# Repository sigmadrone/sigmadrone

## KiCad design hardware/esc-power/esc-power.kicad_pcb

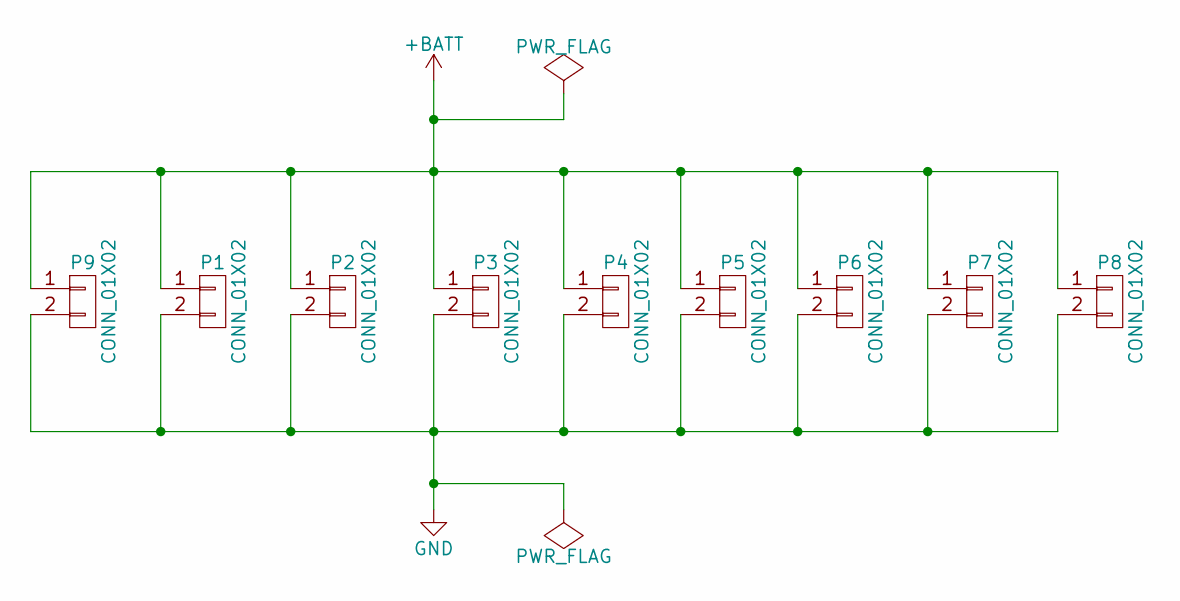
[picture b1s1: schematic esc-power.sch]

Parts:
P1, P2, P3, P4, P5, P6, P7, P8: CONN_01X02; TerminalBlock_Pheonix_PT-3.5mm_2pol
P9: CONN_01X02; WURTH_691219610002

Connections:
+BATT: P1.1, P2.1, P3.1, P4.1, P5.1, P6.1, P7.1, P8.1, P9.1
GND: P1.2, P2.2, P3.2, P4.2, P5.2, P6.2, P7.2, P8.2, P9.2

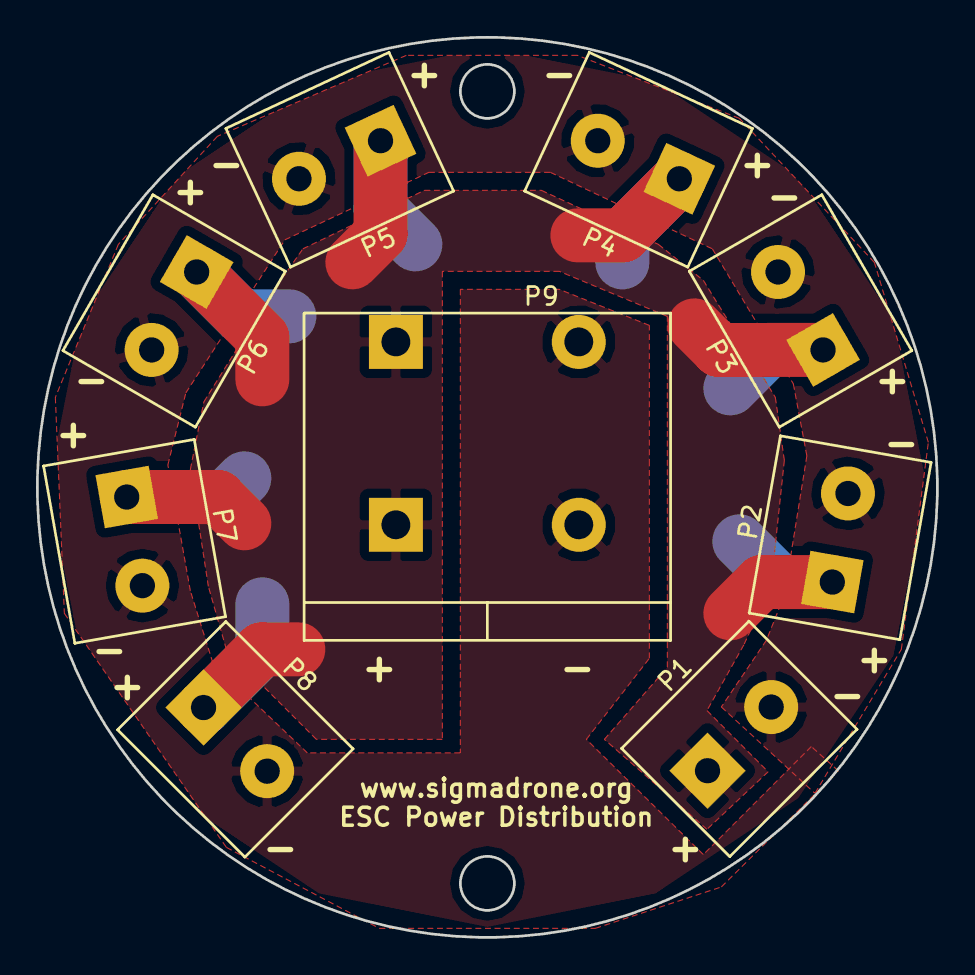
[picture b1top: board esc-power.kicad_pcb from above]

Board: 2 copper layers, 50.0 x 50.0 mm, 9 parts (0 on the bottom side), 2 nets.

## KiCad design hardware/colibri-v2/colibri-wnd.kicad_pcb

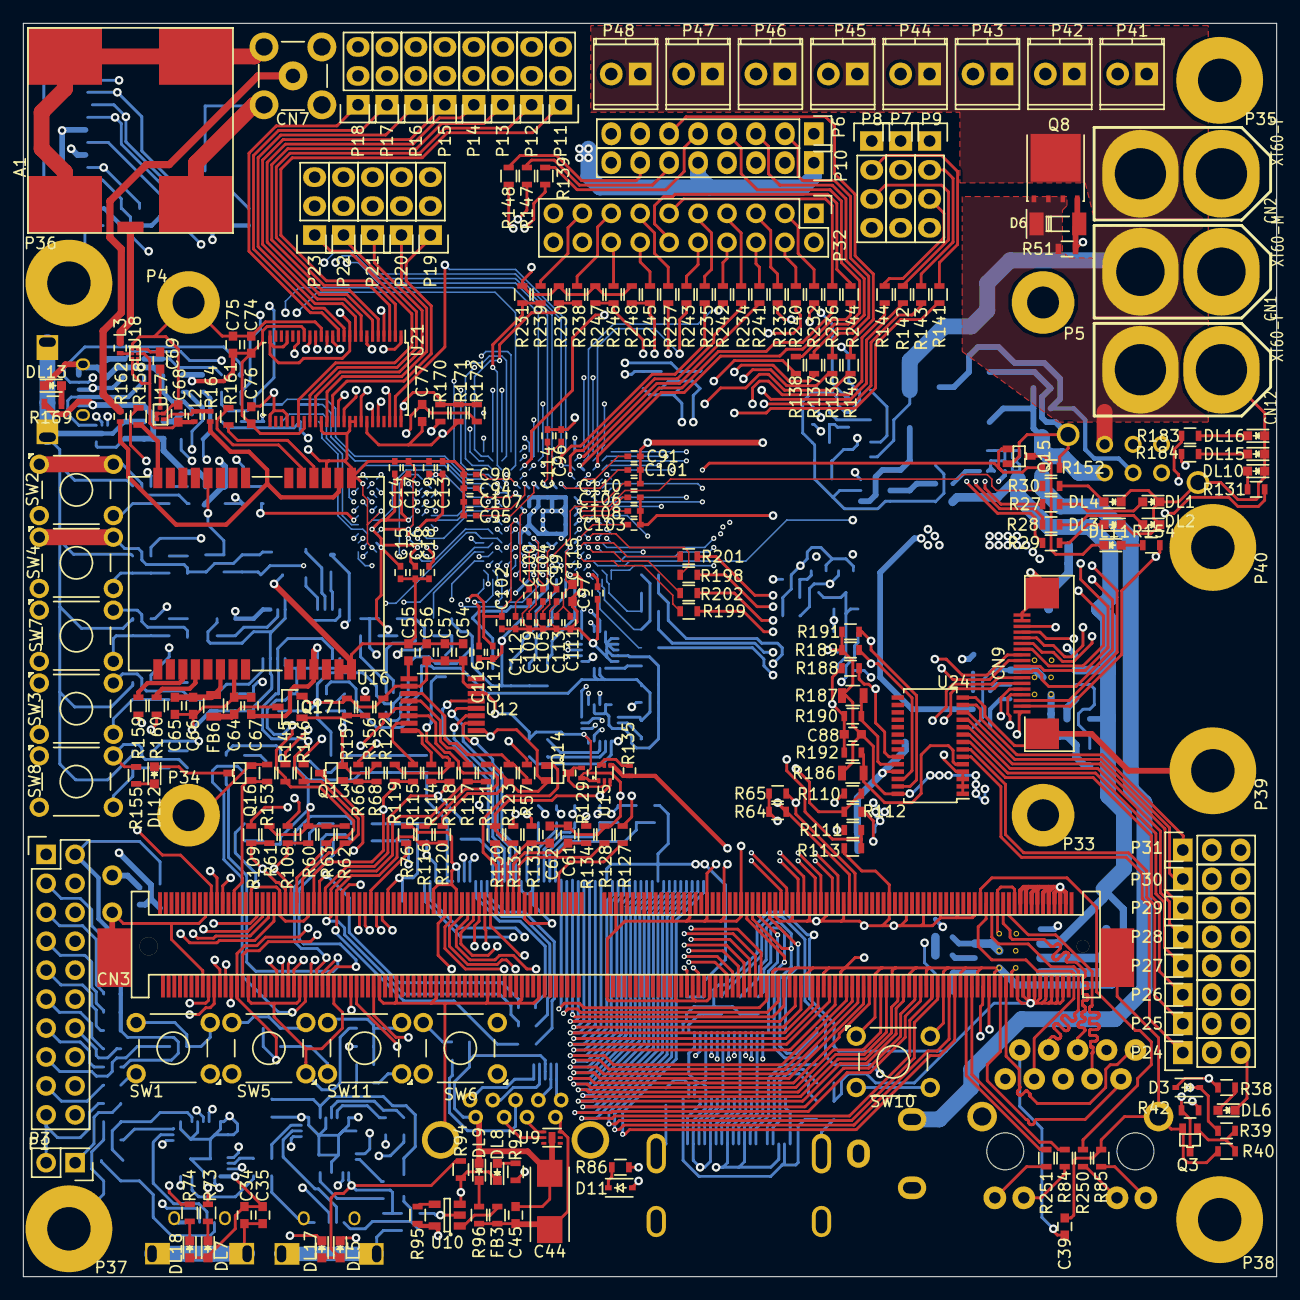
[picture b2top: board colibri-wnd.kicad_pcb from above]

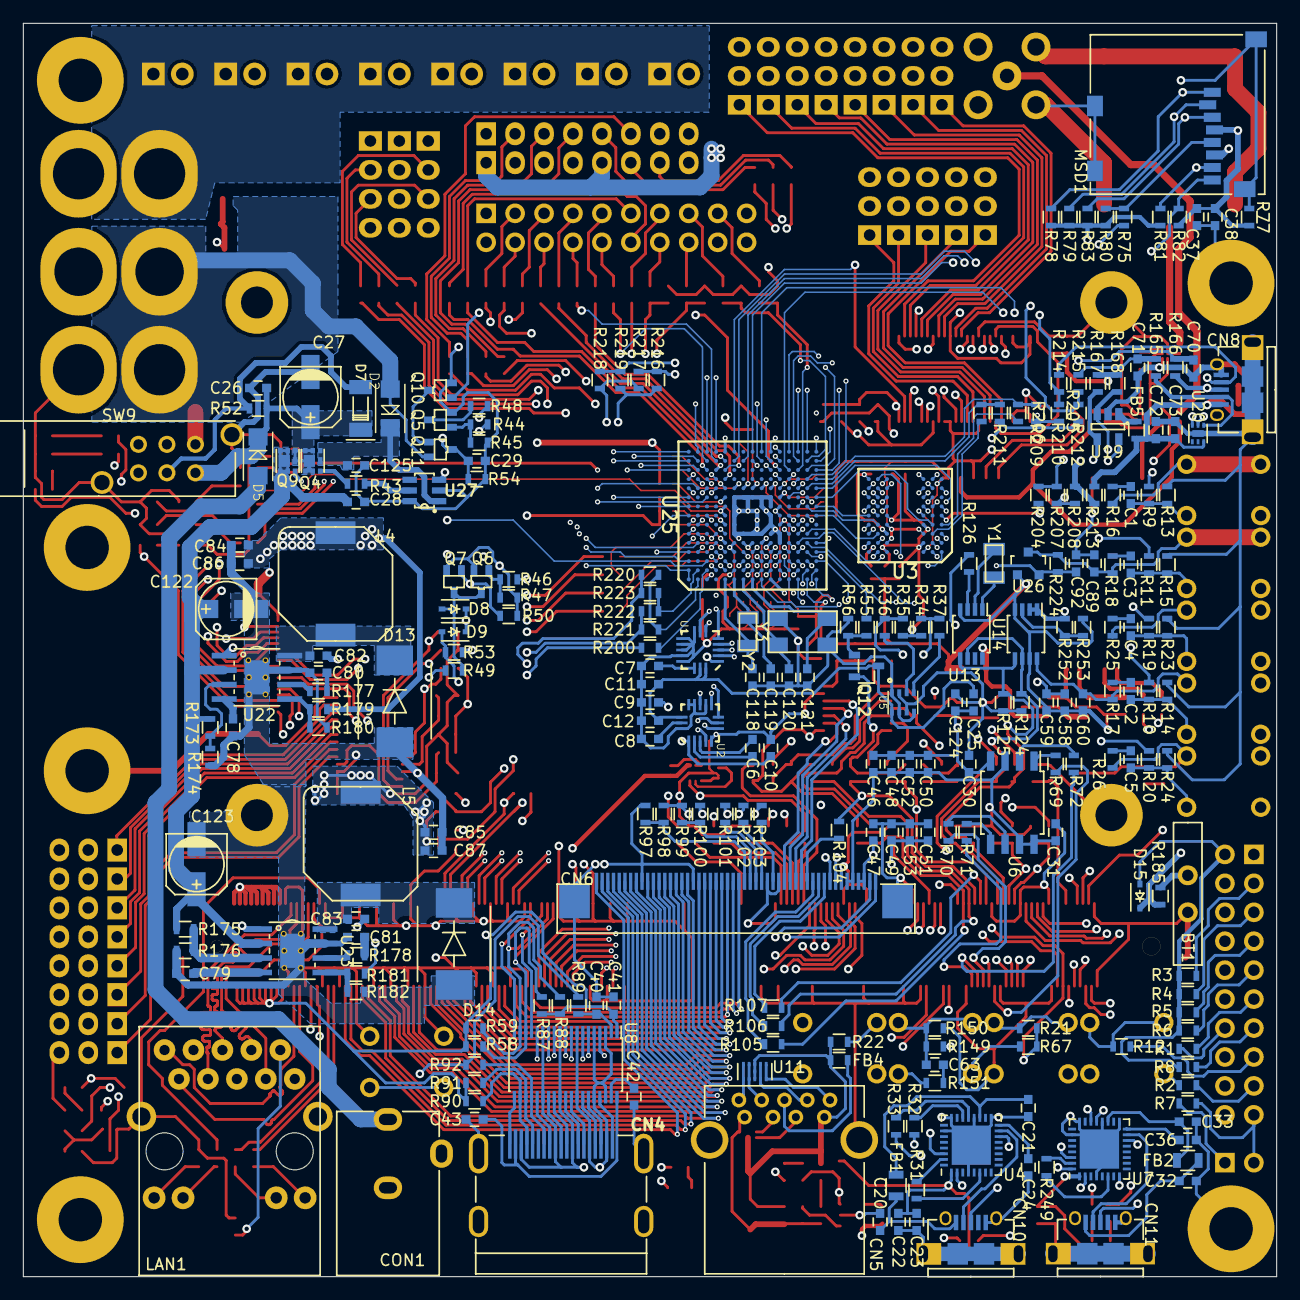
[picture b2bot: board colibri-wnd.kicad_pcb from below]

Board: 6 copper layers, 110.0 x 110.0 mm, 521 parts (247 on the bottom side), 486 nets.

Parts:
A1: ANT1818B00AT1575S
BT1: VL1220-1VC; VL_1220
C1, C2, C3, C4, C5, C25, C63, C92, C124: 100nF/50V; C_0603
C6: 220nF/50V/X7R; C_0603
C7: 10nF/50V/X7R; C_0603
C8: 4u7/6V3/X5R; C_0603
C9, C10, C21, C23, C24, C26, C28, C29, C31, C33, C35, C36, C37, C39, C40, C41, C42, C43, C45, C48, C49, C52, C53, C54, C55, C56, C59, C60, C66, C67, C68, C73, C74, C75, C76, C77, C78, C79, C82, C83, C89, C125: 100nF/50V/X7R; C_0603
C11, C12, C20, C22, C32, C34, C38, C58, C65, C72, C84, C85, C86, C87, C88, C115: 10uF/16V/X5R; C_0603
C13, C14, C15, C16, C17, C18, C19, C94, C95, C96, C97, C99, C100, C101, C102, C103, C104, C105, C106, C107, C108, C109, C110, C111, C112, C113, C114, C117: 100nF/16V; C_0402
C27, C122, C123: 22uF/35V; c_elec_5x5.7
C30: 2u2/10V/X5R; C_0603
C44: 220uF/10%/6V3; TantalC_SizeC_EIA-6032_Reflow
C46, C47: 47uF/25V/X7R; C_0603
C50, C51, C57, C64: 1uF/25V/X7R; C_0603
C61, C62, C70, C71: 47pF/100V/C0G; C_0603
C69: 100pF/50V/1%; C_0603
C80, C81: 470pF/50V/X7R; C_0603
C90, C91, C116: 2u2/10V; C_0402
C118, C119: 15pF/50V/NPO; C_0603
C120, C121: 10pF/50V/NPO; C_0603
CN1: XT60-M; xt60-M
CN2, CN12: XT60-F; xt60-F
CN3: AS0B821-S78B-7H
CN4: HDMI_A; MOLEX_500254_1927
CN5: 692_121_030_100; 692121030100
CN6: Wurth-68715014522-LCD; 68715014522
CN7: MOLEX_73366_0061
CN8, CN10, CN11: 629_105_150_921; WURTH_629105150921
CN9: Wurth-68711814522; 68711814522
CON1: PJ-102AH
D2, D5: VS-15MQ040NTRPBF; DO-214AC
D3, D8, D9, D11, D15: BAS316; SOD-323
D6, D7: BZV55-C18; SOD-80
D13, D14: B560C-13-F; DO-214AB-B560C-13-F
DL1, DL2, DL5, DL7, DL9, DL10, DL11, DL13, DL16: GREEN; LED_0603
DL3, DL4, DL6, DL8, DL12, DL15, DL17, DL18: RED; LED_0603
FB1, FB2: BEAD/0.6OHM/0.2A; R_0805
FB3, FB4, FB5: BEAD/0.045OHM/2A; R_0603
FB6: BEAD/330ohm/100MHz; R_0805
L2: 47nH/0A2/5%; R_0402
L3: 5.6nH/800mA/±0.5nH/0402; R_0402
L4, L5: 3u3/4A6; 7447713033
LAN1: 7499111446; WURTH_7499111446
MSD1: WURTH_693071010811
P1, P32: CONN_02X10; Pin_Header_Straight_2x10
P3: CONN_02X01; Pin_Header_Straight_2x01
P4, P5, P33, P34: ECM00870-L
P6, P10: CONN_01X08; Pin_Header_Straight_1x08
P7, P8, P9: CONN_01X04; Pin_Header_Straight_1x04
P11, P12, P13, P14, P15, P16, P17, P18, P19, P20, P21, P22, P23, P24, P25, P26, P27, P28, P29, P30, P31: CONN_01X03; Pin_Header_Straight_1x03
P35, P36, P37, P38, P39, P40: STANDOFF; STANDOFF-6-32
P41, P42, P43, P44, P45, P46, P47, P48: MPT-2.54; TerminalBlock_Pheonix_MPT-2.54mm_2pol
Q3, Q5, Q6, Q7, Q13, Q15, Q16: BSS138PW; SOT-323
Q4, Q9: FDMA530PZ
Q8: AP6681GMT-HF-3TR; AP6681GMT-HF-3
Q10: PDTC123JU; SOT-323
Q11, Q14: PDTA123JU; SOT-323
Q12, Q17: IRLML6402TRPBF; SOT23_IRLML6402
R1, R2, R3, R4, R5, R6, R8, R22, R39, R40, R42, R45, R47, R49, R51, R53, R67, R68, R76, R77, R78, R79, R80, R81, R82, R83, R89, R94, R95, R112, R113, R118, R119, R120, R121, R122, R123, R127, R152, R153, R167, R168, R188, R190, R192, R224: 10K/5%; R_0603
R7, R57, R85, R126, R128, R198, R199, R200, R201, R202, R204, R205, R206, R208, R210, R212, R217, R219, R221, R223, R249, R251, R252: 0R/5%; R_0603
R9, R10, R11, R12, R16, R17, R18, R19, R20, R21, R25, R26, R43, R44, R46, R48, R66, R149, R151: 100R/5%; R_0603
R13, R14, R15, R23, R24, R50, R52, R54, R56, R150: 100K/5%; R_0603
R27, R28, R29, R30, R86: 1K/5%; R_0603
R31, R98: N/A; R_0603
R32, R33, R73, R74: 270R/5%; R_0603
R34, R35, R38, R58, R59, R60, R61, R62, R63, R64, R65, R87, R88, R189, R191, R230, R231, R247, R248: 2k2/5%; R_0603
R36, R37, R55, R69, R70, R71, R72, R75, R97, R99, R100, R101, R102, R103, R104, R105, R106, R107, R108, R109, R110, R111, R114, R115, R116, R117, R130, R132, R133, R134, R136, R137, R138, R139, R140, R141, R142, R143, R144, R145, R146, R147, R148, R156, R158, R159, R160, R165, R166, R232, R233, R234, R235, R236, R237, R238, R239, R240, R241, R242, R243, R244, R245, R246: 22R/5%; R_0603
R84, R250: 330R/5%; R_0603
R90, R91: 1k8/5%; R_0603
R92: 27K/5%; R_0603
R93: 620R/5%; R_0603
R96, R169: 1k2/5%; R_0603
R124, R125: 2k2/5% [NA]; R_0603
R129: 100K/1%; R_0402
R131: 1k1/5%; R_0603
R135: 47K/1%; R_0402
R154: 360R; R_0603
R155: 750R; R_0603
R157: 100k/5%; R_0603
R161: 10R/5%; R_0603
R162, R164: 0R/5%; R_0402
R170: 0R[NA]; R_0603
R171: 10K/5%[NA]; R_0603
R172: 0R; R_0603
R173, R174, R175, R176, R177, R178: 150K/5%; R_0603
R179, R181: 10K2/1%; R_0603
R180: 1K96/1%; R_0603
R182: 3K24/1%; R_0603
R183: 1k5/5%; R_0603
R184: 750R/5%; R_0603
R185: 470R/5%; R_0603
R186, R187: 0R/1%; R_0805
R207, R209, R211, R213, R214, R215, R216, R218, R220, R222, R253: 0R/5%[NA]; R_0603
SW1, SW2, SW3, SW4, SW5, SW6, SW7, SW8, SW10, SW11: OMRON B3F-1070; SW_TH_Tactile_Omron_B3F-10xx_6x6
SW9: ALPS-SPPJ320600; SPPJ320600
U1: L3GD20HTR; LGA16-3MM_LONG_PADS
U2: LSM303DTR; LGA16-3MM_LONG_PADS
U3: IS42S16400J-7BLI; tfbga-54-35
U4, U7: FT232RQ; QFN-32-1EP_5x5mm_Pitch0.5mm
U5: BMP280; BMP280_LGA-8
U6: M25P32-VMW6TG; SOIJ-8_5.3x5.3mm_Pitch1.27mm
U8: TPD12S521DBTR; TSSOP-38_4.4x9.7mm_Pitch0.5mm
U9, U20: VBUS053CZ-HAF-G-08; VBUS053CZ-HAF
U10: TPS2065CDBVT; SOT-23-5
U11: VBUS054CD-FHI-GS08; VBUS054CD-FHI
U12: TSC2046IPWR; TSSOP-16_4.4x5mm_Pitch0.65mm
U13: PCF8563TS; TSSOP-8_3x3mm_Pitch0.65mm
U14: BR24L02FVM-WTR; TSSOP-8_3x3mm_Pitch0.65mm
U15: NTZD3155C; SOT-563_NTZD3155C
U16: LEA-6S; LEA-6
U17: SF1186K-3
U18: BGA825L6S; TSLP-6-3
U19: TPS2061CDBVT; SOT-23-5
U21: SN74LVC162244A; TSSOP-48_6.1x12.5mm_Pitch0.5mm
U22, U23: TPS54332DDA; TPS54332DDAR
U24: PCA9685PW; TSSOP-28_4.4x9.7mm_Pitch0.65mm
U25: STM32F429NI; tfbga-216-35
U26: TLV803SDBZT; SOT-23
U27: LTC4412; SOT23-6_LTC4412
Y1, Y2: 32.768KHZ; ABS07
Y3: ABMM2-MHz; ABMM2

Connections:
+3V3: C9.1, C10.1, C13.1, C14.1, C15.1, C16.1, C17.1, C18.1, C19.1, C22.2, C23.2, C30.1, C31.2, C34.2, C35.2, C37.1, C38.1, C46.1, C48.1, C50.1, C52.1, C54.1, C56.1, C57.1, C60.2, C74.1, C75.1, C76.1, C77.1, C85.1, C87.1, C88.2, C89.2, C94.2, C95.2, C96.2, C99.2, C100.2, C101.2, C102.2, C103.2, C104.2, C105.2, C106.2, C107.2, C108.2, C109.2, C110.2, C111.2, C112.2, C113.2, C114.2, C115.1, C116.2, C117.1, C124.1, CN6.45, CN6.46, CN9.1, D11.2, D15.2, DL5.2, DL7.2, DL17.2, DL18.2, L5.2, MSD1.4, P1.1, P1.2, P6.1, P7.1, P9.1, P10.1, P10.5, P32.1, P32.2, Q12.2, Q14.2, Q17.2, R3.1, R4.1, R5.1, R6.1, R8.1, R16.1, R17.1, R18.1, R25.1, R26.1, R34.1, R35.1, R42.1, R53.1, R60.1, R61.1, R62.1, R63.1, R64.1, R65.1, R67.1, R77.1, R78.1, R79.1, R80.1, R81.1, R82.1, R83.1, R89.1, R92.1, R93.1, R94.1, R112.2, R118.1, R119.1, R120.1, R121.1, R122.1, R123.1, R124.1, R125.1, R127.1, R151.1, R154.1, R155.1, R157.1, R167.1, R168.1, R171.1, R181.1, R184.1, R186.2, R187.2, R189.1, R191.1, R224.1, R230.1, R231.1, R247.1, R248.1, R252.1, SW2.1, SW2.2, SW3.1, SW3.2, SW4.1, SW4.2, SW6.1, SW6.2, SW7.1, SW7.2, SW8.1, SW8.2, SW11.1, SW11.2, U1.1, U2.1, U3.A7, U3.A9, U3.B3, U3.C7, U3.D3, U3.E7, U3.J9, U4.1, U5.2, U5.6, U6.3, U6.7, U6.8, U7.1, U12.1, U12.7, U12.10, U14.1, U14.2, U14.8, U21.7, U21.18, U21.31, U21.42, U24.28, U25.E5, U25.E7, U25.E8, U25.E9, U25.E10, U25.F4, U25.F5, U25.F11, U25.G5, U25.G11, U25.H5, U25.H11, U25.J5, U25.J11, U25.K5, U25.K11, U25.L7, U25.L8, U25.L9, U25.L10, U25.P1, U25.R1, U26.3
+5V: C41.2, C47.1, C49.1, C51.1, C53.1, C84.1, C86.1, CN3.1E2, CN3.1E3, CN3.1E4, CN3.1E5, CN3.1E6, CN3.1E7, CN3.1E8, CN3.1E9, CN3.1E10, CN3.2E2, CN3.2E3, CN3.2E4, CN3.2E5, CN3.2E6, CN3.2E7, CN3.2E8, CN3.2E9, CN3.2E10, CN6.47, CN6.48, L4.2, P7.4, P8.1, P11.2, P12.2, P13.2, P14.2, P15.2, P16.2, P17.2, P18.2, P19.2, P20.2, P21.2, P22.2, P23.2, P24.2, P25.2, P26.2, P27.2, P28.2, P29.2, P30.2, P31.2, R58.1, R59.1, R87.1, R88.1, R90.1, R91.1, R95.1, R135.2, R179.1, R183.2, U8.1, U10.5, U15.4, U19.5
+BATT: CN1.P, CN12.P, D2.2, D6.1, Q8.1, Q8.2, Q8.3, Q11.2, R51.1, SW9.4
/Cortex FTDI Interface/C_FTDI_RXD: U4.2, U25.B6
/Cortex FTDI Interface/C_FTDI_TXD: U4.30, U25.B5
/External Sensors/C_I2C2_SCL: R246.1, R247.2, U25.H4
/External Sensors/C_I2C2_SDA: R245.1, R248.2, U25.J3
/External Sensors/C_I2C3_SCL: R231.2, R239.1, U25.N13
/External Sensors/C_I2C3_SDA: R230.2, R238.1, U25.P14
/External Sensors/C_SPI2_CLK: R242.1, U25.D14
/External Sensors/C_SPI2_MISO: R243.1, U25.C14
/External Sensors/C_SPI2_MOSI: R244.1, U25.C13
/External Sensors/C_SPI2_NSS1: R241.1, U25.E14
/External Sensors/C_SPI2_NSS2: R240.1, U25.C3
/External Sensors/EXT_GPIO_1: R232.1, U25.P13
/External Sensors/EXT_GPIO_2: R233.1, U25.M15
/External Sensors/EXT_GPIO_3: R234.1, U25.E12
/External Sensors/EXT_GPIO_4: R235.1, U25.E13
/External Sensors/EXT_GPIO_5: R236.1, U25.D13
/External Sensors/EXT_GPIO_6: R237.1, U25.K2
/GPS/GPS_RXD(3V3): R160.2, U25.B14
/GPS/GPS_TIME_PULSE: R158.2, U25.A8
/JTAG/SWD/JTAG_POWER: P1.19, P3.2, R7.2
/JTAG/SWD/JTAG_POWER_ON: P3.1, R7.1, R46.2
/JTAG/SWD/RESET#: C92.1, P1.15, R12.2, R224.2, U25.J1, U26.2
/JTAG/SWD/TCK/SWCLK: P1.9, R6.2, U25.A14
/JTAG/SWD/TDI: P1.5, R4.2, U25.A13
/JTAG/SWD/TDO/SWO: P1.13, R8.2, U25.A10
/JTAG/SWD/TMS/SWDIO: P1.7, R5.2, U25.A15
/JTAG/SWD/TRST: P1.3, R3.2, U25.A9
/Leds/Buttons/BOOT0: R22.2, SW6.3, SW6.4, U25.E6
/Leds/Buttons/BUTTON_0: R9.2, U25.M5
/Leds/Buttons/BUTTON_1: R10.2, U25.M13
/Leds/Buttons/BUTTON_2: R11.2, U25.M12
/Leds/Buttons/BUTTON_3: R19.2, U25.J15
/Leds/Buttons/BUTTON_4: R20.2, U25.J14
/Leds/Buttons/LED1: R27.2, U25.E3
/Leds/Buttons/LED2: R28.2, U25.G3
/Leds/Buttons/LED3: R29.2, U25.H3
/Leds/Buttons/LED4: R30.2, U25.G4
/Leds/Buttons/MODULE_RESET#: CN3.254, R21.2, R67.2, U25.N4
/MEMS/MEMS_ACC_INT1: U2.11, U25.D12
/MEMS/MEMS_ACC_INT2: U2.9, U25.A12
/MEMS/MEMS_GYR_INT1: U1.7, U25.N2
/MEMS/MEMS_GYR_INT2: U1.6, U25.R2
/MEMS/V_SENS1: C11.1, C12.1, C25.1, Q12.3, U1.15, U1.16, U2.14, U5.8
/Power Control/ADAPTER_AV#: Q3.3, R42.2, U25.L4
/Power Control/BAT_MSRMNT: C29.1, Q11.3, R54.1, U25.M4
/Power Control/MSRMNT_ON: Q10.1, U25.N14
/Power Control/PWR_BTN_READ: D9.2, R53.2, U25.P15
/Power Control/PWR_ON: Q7.1, R50.1, U25.N15
/Power Control/VH_CTRL: R44.2, U25.R5
/Power Control/Vsys: C28.1, C122.1, C123.1, Q9.1, Q9.2, Q9.5, Q9.6, Q9.7, R173.1, R175.1, U22.2, U23.2
/STM32F4 SDRAM/FMC_A0: U3.H7, U25.D2
/STM32F4 SDRAM/FMC_A1: U3.H8, U25.E2
/STM32F4 SDRAM/FMC_A2: U3.J8, U25.G2
/STM32F4 SDRAM/FMC_A3: U3.J7, U25.H2
/STM32F4 SDRAM/FMC_A4: U3.J3, U25.J2
/STM32F4 SDRAM/FMC_A5: U3.J2, U25.K3
/STM32F4 SDRAM/FMC_A6: U3.H3, U25.M6
/STM32F4 SDRAM/FMC_A7: U3.H2, U25.N6
/STM32F4 SDRAM/FMC_A8: U3.H1, U25.P6
/STM32F4 SDRAM/FMC_A9: U3.G3, U25.M8
/STM32F4 SDRAM/FMC_A10: U3.H9, U25.N7
/STM32F4 SDRAM/FMC_A11: U3.G2, U25.M7
/STM32F4 SDRAM/FMC_B0: U3.G7, U25.N12
/STM32F4 SDRAM/FMC_B1: U3.G8, U25.N11
/STM32F4 SDRAM/FMC_D0: U3.A8, U25.L12
/STM32F4 SDRAM/FMC_D1: U3.B9, U25.K13
/STM32F4 SDRAM/FMC_D2: U3.B8, U25.B12
/STM32F4 SDRAM/FMC_D3: U3.C9, U25.C12
/STM32F4 SDRAM/FMC_D4: U3.C8, U25.R8
/STM32F4 SDRAM/FMC_D5: U3.D9, U25.N9
/STM32F4 SDRAM/FMC_D6: U3.D8, U25.P9
/STM32F4 SDRAM/FMC_D7: U3.E9, U25.R9
/STM32F4 SDRAM/FMC_D8: R204.2, U3.E1
/STM32F4 SDRAM/FMC_D9: U3.D2, U25.R10
/STM32F4 SDRAM/FMC_D10: R205.2, U3.D1
/STM32F4 SDRAM/FMC_D11: R206.2, U3.C2
/STM32F4 SDRAM/FMC_D12: U3.C1, U25.R11
/STM32F4 SDRAM/FMC_D13: U3.B2, U25.L15
/STM32F4 SDRAM/FMC_D14: U3.B1, U25.L14
/STM32F4 SDRAM/FMC_D15: U3.A2, U25.K15
/STM32F4 SDRAM/FMC_NBL0: U3.E8, U25.A6
/STM32F4 SDRAM/FMC_NBL1: U3.F1, U25.A5
/STM32F4 SDRAM/FMC_SDCKE0: U3.F3, U25.K4
/STM32F4 SDRAM/FMC_SDCLK: U3.F2, U25.H14
/STM32F4 SDRAM/FMC_SDNCAS: U3.F7, U25.B7
/STM32F4 SDRAM/FMC_SDNE0: U3.G9, U25.J4
/STM32F4 SDRAM/FMC_SDNRAS: U3.F8, U25.P8
/STM32F4 SDRAM/FMC_SDNWE: U3.F9, U25.M2
/Sensors Power Control/V_SENS_CTRL: R55.2, U25.R4
/Servo Motors PWM output/SRV_PWM_0: U21.47, U25.F15
/Servo Motors PWM output/SRV_PWM_1: R207.2, R208.2, U21.46
/Servo Motors PWM output/SRV_PWM_2: R209.2, R210.2, U21.44
/Servo Motors PWM output/SRV_PWM_3: R211.2, R212.2, U21.43
/Servo Motors PWM output/SRV_PWM_4: U21.41, U25.H15
/Servo Motors PWM output/SRV_PWM_6: U21.38, U25.G14
/Servo Motors PWM output/SRV_PWM_7: U21.37, U25.F14
/USB_OTG_FS/OTG_FS_DM: C71.1, R165.2, R215.2
/USB_OTG_FS/OTG_FS_DP: C70.1, R166.2, U25.B15
/USB_OTG_FS/OTG_FS_ID: CN8.4, R214.2, U20.3
/USB_OTG_FS/OTG_FS_VBUS: C72.1, C73.1, CN8.1, FB5.2, R169.2, R213.2, U20.6
/Wandboard Connector/CSPI1_CS1: CN3.230, R69.1
/Wandboard Connector/DISP0_DAT0: CN3.2, CN6.1
/Wandboard Connector/DISP0_DAT1: CN3.4, CN6.2
/Wandboard Connector/DISP0_DAT2: CN3.8, CN6.3
/Wandboard Connector/DISP0_DAT3: CN3.10, CN6.4
/Wandboard Connector/DISP0_DAT4: CN3.14, CN6.5
/Wandboard Connector/DISP0_DAT5: CN3.16, CN6.6
/Wandboard Connector/DISP0_DAT6: CN3.20, CN6.7
/Wandboard Connector/DISP0_DAT7: CN3.22, CN6.8
/Wandboard Connector/DISP0_DAT8: CN3.26, CN6.10
/Wandboard Connector/DISP0_DAT9: CN3.28, CN6.11
/Wandboard Connector/DISP0_DAT10: CN3.32, CN6.12
/Wandboard Connector/DISP0_DAT11: CN3.34, CN6.13
/Wandboard Connector/DISP0_DAT12: CN3.36, CN6.14
/Wandboard Connector/DISP0_DAT13: CN3.38, CN6.15
/Wandboard Connector/DISP0_DAT14: CN3.40, CN6.16
/Wandboard Connector/DISP0_DAT15: CN3.44, CN6.17
/Wandboard Connector/DISP0_DAT16: CN3.46, CN6.19
/Wandboard Connector/DISP0_DAT17: CN3.50, CN6.20
/Wandboard Connector/DISP0_DAT18: CN3.52, CN6.21
/Wandboard Connector/DISP0_DAT19: CN3.56, CN6.22
/Wandboard Connector/DISP0_DAT20: CN3.58, CN6.23
/Wandboard Connector/DISP0_DAT21: CN3.62, CN6.24
/Wandboard Connector/DISP0_DAT22: CN3.64, CN6.25
/Wandboard Connector/DISP0_DAT23: CN3.68, CN6.26
/Wandboard Connector/MODULE_ON/OFF: R66.2, U25.R3
/Wandboard Connector/PWR_BTN(ON/OFF): CN3.252, Q13.3
/Wandboard Connector/RTC_INT: CN3.96, R126.1, U25.C8
/Wandboard Connector/R_NANDF_CS2: CN3.92, R57.1
/Wandboard Connector/WB_GPIO1: CN3.256, R198.2
/Wandboard Connector/WB_GPIO2: CN3.258, R199.2
/Wandboard Connector/WB_GPIO3: CN3.260, R200.2
/Wandboard Connector/WB_GPIO4: CN3.262, R201.2
/Wandboard Connector/WB_GPIO5: CN3.264, R202.2
/Wandboard Connector/WB_SPI_CLK: CN3.226, R70.1, U25.A3
/Wandboard Connector/WB_SPI_CS: CN3.228, U25.A1, U25.A2
/Wandboard Connector/WB_SPI_MISO: CN3.224, R72.1, R221.2, R222.2
/Wandboard Connector/WB_SPI_MOSI: CN3.222, R71.1, R220.2, R223.2
/Wandboard Connector/Wandboard EEPROM/EEPROM_SCL: CN3.231, R62.2, R124.2, R146.1, U13.6, U14.6
/Wandboard Connector/Wandboard EEPROM/EEPROM_SDA: CN3.233, R63.2, R125.2, R145.1, U13.5, U14.5
/Wandboard Connector/Wandboard Ethernet/LED1_ACT: CN3.3E7, R250.2
/Wandboard Connector/Wandboard Ethernet/LED1_nLINK100: CN3.4E8, R84.2
/Wandboard Connector/Wandboard Ethernet/LED1_nLINK1000: CN3.4E9, R251.2
/Wandboard Connector/Wandboard Ethernet/TRD0_N: CN3.4E3, LAN1.2
/Wandboard Connector/Wandboard Ethernet/TRD0_P: CN3.4E2, LAN1.1
/Wandboard Connector/Wandboard Ethernet/TRD1_N: CN3.4E6, LAN1.6
/Wandboard Connector/Wandboard Ethernet/TRD1_P: CN3.4E5, LAN1.3
/Wandboard Connector/Wandboard Ethernet/TRD2_N: CN3.3E3, LAN1.5
/Wandboard Connector/Wandboard Ethernet/TRD2_P: CN3.3E2, LAN1.4
/Wandboard Connector/Wandboard Ethernet/TRD3_N: CN3.3E6, LAN1.8
/Wandboard Connector/Wandboard Ethernet/TRD3_P: CN3.3E5, LAN1.7
/Wandboard Connector/Wandboard FTDI Interface/WB_FTDI_CTS: CN3.241, U7.8
/Wandboard Connector/Wandboard FTDI Interface/WB_FTDI_DSR: R249.1, U7.6
/Wandboard Connector/Wandboard FTDI Interface/WB_FTDI_DTR: R249.2, U7.31
/Wandboard Connector/Wandboard FTDI Interface/WB_FTDI_RTS: CN3.247, U7.32
/Wandboard Connector/Wandboard FTDI Interface/WB_FTDI_RXD: CN3.243, U7.2
/Wandboard Connector/Wandboard FTDI Interface/WB_FTDI_TXD: CN3.245, U7.30
/Wandboard Connector/Wandboard HDMI/DDC_SCL(5V): CN3.75, R58.2, R87.2, R141.1, U8.17
/Wandboard Connector/Wandboard HDMI/HDMI1_HPD: CN3.67, U8.19
/Wandboard Connector/Wandboard HDMI/HDMI_CEC_IN: CN3.71, R86.2, U8.16
/Wandboard Connector/Wandboard HDMI/HDMI_CLK+: CN3.43, U8.13
/Wandboard Connector/Wandboard HDMI/HDMI_CLK-: CN3.45, U8.15
/Wandboard Connector/Wandboard HDMI/HDMI_D0+: CN3.49, U8.10
/Wandboard Connector/Wandboard HDMI/HDMI_D0-: CN3.51, U8.12
/Wandboard Connector/Wandboard HDMI/HDMI_D1+: CN3.55, U8.7
/Wandboard Connector/Wandboard HDMI/HDMI_D1-: CN3.57, U8.9
/Wandboard Connector/Wandboard HDMI/HDMI_D2+: CN3.61, U8.4
/Wandboard Connector/Wandboard HDMI/HDMI_D2-: CN3.63, U8.6
/Wandboard Connector/Wandboard LCD/DISP0_CLK: CN3.70, R103.2
/Wandboard Connector/Wandboard LCD/DISP0_CNTRST: CN3.76, R98.2, R99.2
/Wandboard Connector/Wandboard LCD/DISP0_DRDY: CN3.78, R100.2
/Wandboard Connector/Wandboard LCD/DISP0_HSYNC: CN3.72, R101.2
/Wandboard Connector/Wandboard LCD/DISP0_PWREN: CN3.82, R111.2
/Wandboard Connector/Wandboard LCD/DISP0_RESET: CN3.80, R110.2
/Wandboard Connector/Wandboard LCD/DISP0_VSYNC: CN3.74, R102.2
/Wandboard Connector/Wandboard LCD/TOUCH_X1: CN6.34, U12.2
/Wandboard Connector/Wandboard LCD/TOUCH_X2: CN6.35, U12.4
/Wandboard Connector/Wandboard LCD/TOUCH_Y1: CN6.36, U12.3
/Wandboard Connector/Wandboard LCD/TOUCH_Y2: CN6.37, U12.5
/Wandboard Connector/Wandboard LCD/TP_BUSY: CN3.263, R122.2, U12.13
/Wandboard Connector/Wandboard LCD/TP_PENIRQ: R57.2, R123.2, U12.11
/Wandboard Connector/Wandboard OTG to Cortex USB FS2/USB_OGT_DM: C62.1, CN3.159, R133.2
/Wandboard Connector/Wandboard OTG to Cortex USB FS2/USB_OTG_DP: C61.1, CN3.157, R134.2
/Wandboard Connector/Wandboard OTG to Cortex USB FS2/USB_OTG_ID: CN3.155, R128.2
/Wandboard Connector/Wandboard OTG to Cortex USB FS2/USB_OTG_OC: CN3.141, R127.2
/Wandboard Connector/Wandboard OTG to Cortex USB FS2/USB_OTG_PWR_EN#: CN3.163, Q14.1
/Wandboard Connector/Wandboard OTG to Cortex USB FS2/USG_OTG_VBUS: CN3.161, R130.2
/Wandboard Connector/Wandboard SD Card/SD1_CD: CN3.203, MSD1.9, R77.2
/Wandboard Connector/Wandboard SD Card/SD1_CLK: CN3.206, R75.2
/Wandboard Connector/Wandboard SD Card/SD1_CMD: CN3.205, MSD1.3, R83.2
/Wandboard Connector/Wandboard SD Card/SD1_DATA0: CN3.212, MSD1.7, R81.2
/Wandboard Connector/Wandboard SD Card/SD1_DATA1: CN3.209, MSD1.8, R82.2
/Wandboard Connector/Wandboard SD Card/SD1_DATA2: CN3.214, MSD1.1, R78.2
/Wandboard Connector/Wandboard SD Card/SD1_DATA3: CN3.211, MSD1.2, R79.2
/Wandboard Connector/Wandboard SD Card/SD1_WP: CN3.207, R76.1
/Wandboard Connector/Wandboard Service/CSPI2_CLK: CN3.223, R104.2, R114.1, R118.2, R138.1
/Wandboard Connector/Wandboard Service/CSPI2_CS0_DISPLAY: CN3.225, R107.2, R139.1
/Wandboard Connector/Wandboard Service/CSPI2_CS1_TP: CN3.227, R115.1, R119.2, R140.1
/Wandboard Connector/Wandboard Service/CSPI2_MISO: CN3.221, R106.2, R117.1, R121.2, R137.1
/Wandboard Connector/Wandboard Service/CSPI2_MOSI: CN3.219, R105.2, R116.1, R120.2, R136.1
/Wandboard Connector/Wandboard Service/DDC_SCL(5V): CN3.73, R59.2, R88.2, R142.1, U8.18
/Wandboard Connector/Wandboard Service/DISP0_I2C3_SCL(3V3): CN3.235, R60.2, R108.2, R148.1
/Wandboard Connector/Wandboard Service/DISP0_I2C3_SDA(3V3): CN3.237, R61.2, R109.2, R147.1
/Wandboard Connector/Wandboard Service/I2C1_SCL(3V3): CN3.39, R64.2, R144.1
/Wandboard Connector/Wandboard Service/I2C1_SDA(3V3): CN3.37, R65.2, R143.1
/Wandboard Connector/Wandboard Service/WB_BUTTON1: CN3.259, R149.2
/Wandboard Connector/Wandboard Service/WB_LED1: CN3.261, Q15.1, R152.1
/Wandboard Connector/Wandboard Service/WB_LED2: CN3.255, Q16.1, R153.1
/Wandboard Connector/Wandboard USB Host/GND_DRAIN: CN3.171, CN5.7, FB4.1
/Wandboard Connector/Wandboard USB Host/StdA_SSRX+: CN3.167, CN5.6, U11.4, U11.7
/Wandboard Connector/Wandboard USB Host/StdA_SSRX-: CN3.169, CN5.5, U11.5, U11.6
/Wandboard Connector/Wandboard USB Host/StdA_SSTX+: CN3.173, CN5.9, U11.1, U11.10
/Wandboard Connector/Wandboard USB Host/StdA_SSTX-: CN3.175, CN5.8, U11.2, U11.9
/Wandboard Connector/Wandboard USB Host/USB_HOST_DM: CN3.179, CN5.2, U9.1
/Wandboard Connector/Wandboard USB Host/USB_HOST_DP: CN3.181, CN5.3, U9.2
/Wandboard Connector/Wandboard USB Host/USB_HOST_OC: CN3.165, DL8.1, R94.2, U10.3
/cortex/C_OTG_FS_OC: R168.2, U19.3, U25.P5
/cortex/C_OTG_FS_PSO: R167.2, U19.4, U25.N5
/cortex/C_WB_UART_CTS: CN3.234, R217.2, R218.2
/cortex/C_WB_UART_RTS: CN3.240, R216.2, R219.2
/cortex/C_WB_UART_RX: CN3.236, U25.B11
/cortex/C_WB_UART_TX: CN3.238, U25.C10
/cortex/GPS_PWR_CTRL: R156.2, U25.A4
/cortex/GPS_RXD: R159.2, U25.B13
/cortex/IN_PWM_01: U21.13, U25.P4
/cortex/IN_PWM_02: U21.14, U25.P3
/cortex/IN_PWM_03: U21.16, U25.M10
/cortex/IN_PWM_04: U21.17, U25.N3
/cortex/IN_PWM_05: U21.19, U25.P2
/cortex/MEMS_ACC_CS: U2.8, U25.A11
/cortex/MEMS_GYRO_CS: U1.5, U25.M3
/cortex/MEMS_SPI5_MISO: U1.4, U2.7, U25.L3
/cortex/MEMS_SPI5_MOSI: U1.3, U2.6, U25.L2
/cortex/MEMS_SPI5_SCK: U1.2, U2.4, U25.K1
/cortex/OSC-IN: C118.2, U25.E1, Y2.1
/cortex/OSC-OUT: C119.2, U25.F1, Y2.2
/cortex/OTG_HS_DM: R133.1, U25.R14
/cortex/OTG_HS_DP: R134.1, U25.R15
/cortex/OTG_HS_VBUS: R132.1, U25.K14
/cortex/PCA9685_OE: R188.1, U24.23, U25.L13
/cortex/PCA9685_SCL: R189.2, U24.26, U25.P12
/cortex/PCA9685_SDA: R191.2, U24.27, U25.R13
/cortex/PH0: C120.2, U25.G1, Y3.1
/cortex/PH1: C121.2, U25.H1, Y3.3
/cortex/PI6: R198.1, U25.D6
/cortex/PI7: R199.1, U25.D4
/cortex/PI8: R200.1, U25.C2
/cortex/PI9: R201.1, U25.E4
/cortex/PI10: R202.1, U25.D5
/cortex/PS_I2C1_SCL: R34.2, R37.2, U25.A7
/cortex/PS_I2C1_SDA: R35.2, R36.2, U25.B4
/cortex/PWM_SRV_EN: R170.1, U25.D3
/cortex/SPI4_MISO: R220.1, R221.1, U25.B1
/cortex/SPI4_MOSI: R222.1, R223.1, U25.B2
/cortex/TIM1_CH2/FMC_D8: R204.1, R207.1, U25.P10
/cortex/TIM1_CH2/OTG_FS_VBUS: R208.1, R213.1, U25.E15
/cortex/TIM1_CH3/FMC_D10: R205.1, R209.1, U25.R12
/cortex/TIM1_CH3/OTG_FS_ID: R210.1, R214.1, U25.D15
/cortex/TIM1_CH4/FMC_D11: R206.1, R211.1, U25.P11
/cortex/TIM1_CH4/OTG_FS_DM: R212.1, R215.1, U25.C15
/cortex/USART2_CTS: R216.1, R217.1, U25.C11
/cortex/USART2_RTS: R218.1, R219.1, U25.D11
/cortex/VCAP1: C90.2, U25.L11
/cortex/VCAP2: C91.2, U25.E11
GND: A1.2, BT1.2, C7.2, C8.2, C9.2, C10.2, C11.2, C12.2, C13.2, C14.2, C15.2, C16.2, C17.2, C18.2, C19.2, C20.1, C21.1, C22.1, C23.1, C24.2, C25.2, C26.2, C27.2, C28.2, C29.2, C30.2, C31.1, C32.1, C33.1, C34.1, C35.1, C36.2, C37.2, C38.2, C39.2, C40.1, C41.1, C42.1, C43.1, C44.2, C45.2, C46.2, C47.2, C48.2, C49.2, C50.2, C51.2, C52.2, C53.2, C54.2, C55.2, C56.2, C57.2, C58.2, C59.2, C60.1, C61.2, C62.2, C64.1, C65.1, C66.1, C67.1, C68.1, C70.2, C71.2, C72.2, C73.2, C74.2, C75.2, C76.2, C77.2, C78.2, C79.2, C80.2, C81.2, C84.2, C85.2, C86.2, C87.2, C88.1, C89.1, C90.1, C91.1, C92.2, C94.1, C95.1, C96.1, C97.1, C99.1, C100.1, C101.1, C102.1, C103.1, C104.1, C105.1, C106.1, C107.1, C108.1, C109.1, C110.1, C111.1, C112.1, C113.1, C114.1, C115.2, C116.1, C117.2, C118.1, C119.1, C120.1, C121.1, C122.2, C123.2, C124.2, C125.1, CN1.N, CN2.N, CN3.1, CN3.3E1, CN3.3E4, CN3.3E8, CN3.4E1, CN3.4E4, CN3.4E7, CN3.4E10, CN3.6, CN3.7, CN3.12, CN3.13, CN3.18, CN3.19, CN3.24, CN3.25, CN3.30, CN3.41, CN3.42, CN3.47, CN3.48, CN3.53, CN3.54, CN3.59, CN3.60, CN3.65, CN3.66, CN3.77, CN3.83, CN3.88, CN3.89, CN3.94, CN3.95, CN3.100, CN3.101, CN3.121, CN3.124, CN3.148, CN3.153, CN3.154, CN3.166, CN3.177, CN3.184, CN3.185, CN3.198, CN3.201, CN3.204, CN3.217, CN3.220, CN3.229, CN3.232, CN3.239, CN3.249, CN3.250, CN3.265, CN3.266, CN3.P1, CN3.P2, CN4.2, CN4.5, CN4.8, CN4.11, CN4.17, CN4.FN, CN5.4, CN5.10, CN5.11, CN6.9, CN6.18, CN6.31, CN6.33, CN6.44, CN6.FN, CN7.2, CN7.3, CN7.4, CN7.5, CN8.5, CN8.6, CN8.7, CN8.8, CN8.9, CN8.10, CN8.11, CN9.17, CN9.18, CN9.FN, CN10.5, CN10.6, CN10.7, CN10.8, CN10.9, CN10.10, CN10.11, CN11.5, CN11.6, CN11.7, CN11.8, CN11.9, CN11.10, CN11.11, CN12.N, CON1.2, CON1.3, D13.2, D14.2, DL1.1, DL2.1, DL3.1, DL4.1, DL6.1, DL9.1, DL10.1, DL13.1, DL15.1, DL16.1, FB4.2, LAN1.10, LAN1.FN, MSD1.6, MSD1.10, P1.4, P1.6, P1.8, P1.10, P1.12, P1.14, P1.16, P1.18, P1.20, P4.GND, P5.GND, P6.7, P6.8, P7.2, P7.3, P8.4, P9.4, P10.4, P10.8, P11.3, P12.3, P13.3, P14.3, P15.3, P16.3, P17.3, P18.3, P19.3, P20.3, P21.3, P22.3, P23.3, P24.3, P25.3, P26.3, P27.3, P28.3, P29.3, P30.3, P31.3, P32.19, P32.20, P33.GND, P34.GND, P35.GND, P36.GND, P37.GND, P38.GND, P39.GND, P40.GND, P41.2, P42.2, P43.2, P44.2, P45.2, P46.2, P47.2, P48.2, Q3.2, Q5.2, Q6.2, Q7.2, Q10.2, Q13.2, Q15.2, Q16.2, R1.1, R2.1, R13.2, R14.2, R15.2, R22.1, R23.2, R24.2, R40.2, R45.2, R47.2, R50.2, R54.2, R56.2, R68.2, R76.2, R85.2, R97.2, R113.2, R128.1, R129.1, R150.2, R152.2, R153.2, R172.1, R174.2, R176.2, R180.2, R182.2, R188.2, R190.2, R192.2, R253.1, SW1.1, SW1.2, SW5.1, SW5.2, SW9.P1, SW9.P2, SW10.1, SW10.2, U1.8, U1.9, U1.10, U1.11, U1.12, U1.13, U2.5, U2.10, U2.12, U2.13, U2.16, U3.A1, U3.A3, U3.B7, U3.C3, U3.D7, U3.E3, U3.J1, U4.4, U4.17, U4.20, U4.24, U4.26, U4.33, U5.1, U5.5, U5.7, U6.4, U7.4, U7.17, U7.20, U7.24, U7.26, U7.33, U8.3, U8.5, U8.8, U8.11, U8.14, U8.25, U8.28, U8.31, U8.34, U8.36, U9.7, U10.2, U11.3, U11.8, U11.11, U12.6, U13.4, U14.4, U14.7, U15.1, U16.7, U16.13, U16.14, U16.15, U16.17, U16.24, U17.B, U17.D, U17.E, U18.1, U18.4, U19.2, U20.7, U21.4, U21.10, U21.15, U21.21, U21.24, U21.25, U21.28, U21.34, U21.39, U21.40, U22.7, U22.9, U23.7, U23.9, U24.1, U24.2, U24.3, U24.4, U24.14, U24.25, U25.F2, U25.F6, U25.F7, U25.F8, U25.F9, U25.F10, U25.G6, U25.G10, U25.H6, U25.H10, U25.J6, U25.J10, U25.K6, U25.K7, U25.K8, U25.K9, U25.K10, U25.L5, U25.L6, U25.M1, U25.N1, U26.1, U27.2, U27.6, Y3.2, Y3.4
unnamed: A1.1, L3.1
unnamed: BT1.1, R185.2
unnamed: C1.1, R16.2
unnamed: C1.2, R9.1, R13.1, SW2.3, SW2.4
unnamed: C2.1, R17.2
unnamed: C2.2, R10.1, R14.1, SW3.3, SW3.4
unnamed: C3.1, R18.2
unnamed: C3.2, R11.1, R15.1, SW4.3, SW4.4
unnamed: C4.1, R25.2
unnamed: C4.2, R19.1, R23.1, SW7.3, SW7.4
unnamed: C5.1, R26.2
unnamed: C5.2, R20.1, R24.1, SW8.3, SW8.4
unnamed: C6.1, U2.3
unnamed: C6.2, U2.2
unnamed: C7.1, U1.14
unnamed: C8.1, U2.15
unnamed: C20.2, CN10.1, FB1.1
unnamed: C21.2, FB1.2, U4.19
unnamed: C24.1, U4.16
unnamed: C26.1, C27.1, D5.1, D7.1, Q4.1, Q4.2, Q4.5, Q4.6, Q4.7, Q9.4, Q9.8, R52.1, SW9.1
unnamed: C32.2, CN11.1, FB2.1
unnamed: C33.2, FB2.2, U7.19
unnamed: C36.1, U7.16
unnamed: C39.1, LAN1.9
unnamed: C40.2, R89.2, U8.2
unnamed: C42.2, U8.37
unnamed: C43.2, CN4.18, U8.38
unnamed: C44.1, C45.1, CN5.1, FB3.2, R96.2, U9.6
unnamed: C55.1, U12.9
unnamed: C63.1, R151.2
unnamed: C63.2, R149.1, R150.1, SW11.3, SW11.4
unnamed: C64.2, FB6.1, Q17.3
unnamed: C65.2, C66.2, FB6.2, U16.6
unnamed: C68.2, L2.2, U18.2, U18.6
unnamed: C69.1, U17.C
unnamed: C69.2, U18.3
unnamed: C78.1, U22.4
unnamed: C79.1, U23.4
unnamed: C80.1, R177.2
unnamed: C81.1, R178.2
unnamed: C82.1, U22.1
unnamed: C82.2, D13.1, L4.1, U22.8
unnamed: C83.1, U23.1
unnamed: C83.2, D14.1, L5.1, U23.8
unnamed: C125.2, D2.1, Q4.4, Q4.8, U27.1
unnamed: CN4.1, U8.35
unnamed: CN4.3, U8.33
unnamed: CN4.4, U8.32
unnamed: CN4.6, U8.30
unnamed: CN4.7, U8.29
unnamed: CN4.9, U8.27
unnamed: CN4.10, U8.26
unnamed: CN4.12, U8.24
unnamed: CN4.13, R92.2, U8.23
unnamed: CN4.15, R91.2, U8.22
unnamed: CN4.16, R90.2, U8.21
unnamed: CN4.19, U8.20
unnamed: CN6.27, R97.1, R98.1
unnamed: CN6.28, R99.1, R100.1
unnamed: CN6.29, R101.1
unnamed: CN6.30, R102.1
unnamed: CN6.32, R103.1
unnamed: CN6.38, R104.1
unnamed: CN6.39, R105.1
unnamed: CN6.40, R106.1
unnamed: CN6.41, R107.1
unnamed: CN6.42, R108.1
unnamed: CN6.43, R109.1
unnamed: CN6.49, R110.1, R112.1
unnamed: CN6.50, R111.1, R113.1
unnamed: CN7.1, R162.2
unnamed: CN8.2, R165.1, U20.1
unnamed: CN8.3, R166.1, U20.2
unnamed: CN9.2, P32.4, R240.2
unnamed: CN9.3, P32.6, R241.2
unnamed: CN9.4, P32.8, R242.2
unnamed: CN9.5, P32.10, R243.2
unnamed: CN9.6, P32.12, R244.2
unnamed: CN9.7, P32.14, R245.2
unnamed: CN9.8, P32.16, R246.2
unnamed: CN9.9, P32.3, R232.2
unnamed: CN9.10, P32.5, R233.2
unnamed: CN9.11, P32.7, R234.2
unnamed: CN9.12, P32.9, R235.2
unnamed: CN9.13, P32.11, R236.2
unnamed: CN9.14, P32.13, R237.2
unnamed: CN9.15, P32.15, R238.2
unnamed: CN9.16, P32.17, R239.2
unnamed: CN10.2, U4.15
unnamed: CN10.3, U4.14
unnamed: CN11.2, U7.15
unnamed: CN11.3, U7.14
unnamed: CON1.1, D3.2, D5.2, R38.1
unnamed: D3.1, R39.2, U27.3
unnamed: D6.2, Q8.4, R51.2, SW9.5
unnamed: D7.2, Q9.3, R52.2, SW9.2
unnamed: D8.1, D9.1, SW10.3, SW10.4
unnamed: D8.2, Q6.3, Q7.3, R49.2
unnamed: D11.1, R86.1
unnamed: DL1.2, R27.1
unnamed: DL2.2, R28.1
unnamed: DL3.2, R29.1
unnamed: DL4.2, R30.1
unnamed: DL5.1, R32.1
unnamed: DL6.2, R38.2
unnamed: DL7.1, R73.1
unnamed: DL8.2, R93.2
unnamed: DL9.2, R96.1
unnamed: DL10.2, R131.1
unnamed: DL11.1, Q15.3
unnamed: DL11.2, R154.2
unnamed: DL12.1, Q16.3
unnamed: DL12.2, R155.2
unnamed: DL13.2, R169.1
unnamed: DL15.2, R184.2
unnamed: DL16.2, R183.1
unnamed: DL17.1, R33.1
unnamed: DL18.1, R74.1
unnamed: FB3.1, U10.1
unnamed: FB5.1, U19.1
unnamed: L2.1, R164.2, U17.A
unnamed: L3.2, U18.5
unnamed: LAN1.11, R85.1
unnamed: LAN1.12, R250.1
unnamed: LAN1.13, R84.1
unnamed: LAN1.14, R251.1
unnamed: MSD1.5, R75.1, R80.2
unnamed: P1.11, R1.2
unnamed: P1.17, R2.2
unnamed: P6.2, R136.2
unnamed: P6.3, R137.2
unnamed: P6.4, R138.2
unnamed: P6.5, R139.2
unnamed: P6.6, R140.2
unnamed: P8.2, R141.2
unnamed: P8.3, R142.2
unnamed: P9.2, R143.2
unnamed: P9.3, R144.2
unnamed: P10.2, R145.2
unnamed: P10.3, R146.2
unnamed: P10.6, R147.2
unnamed: P10.7, R148.2
unnamed: P11.1, U21.2
unnamed: P12.1, U21.3
unnamed: P13.1, U21.5
unnamed: P14.1, U21.6
unnamed: P15.1, U21.8
unnamed: P16.1, U21.9
unnamed: P17.1, U21.11
unnamed: P18.1, U21.12
unnamed: P19.1, U21.36
unnamed: P20.1, U21.35
unnamed: P21.1, U21.33
unnamed: P22.1, U21.32
unnamed: P23.1, U21.30
unnamed: P24.1, U24.6
unnamed: P25.1, U24.7
unnamed: P26.1, U24.8
unnamed: P27.1, U24.9
unnamed: P28.1, U24.10
unnamed: P29.1, U24.11
unnamed: P30.1, U24.12
unnamed: P31.1, U24.13
unnamed: Q3.1, R39.1, R40.1
unnamed: Q4.3, R43.2
unnamed: Q5.1, R44.1, R45.1
unnamed: Q5.3, R48.2
unnamed: Q6.1, R46.1, R47.1
unnamed: Q10.3, Q11.1
unnamed: Q12.1, R55.1, R56.1
unnamed: Q13.1, R66.1, R68.1
unnamed: Q14.3, R129.2, U15.2
unnamed: Q17.1, R156.1, R157.2
unnamed: R12.1, SW1.3, SW1.4
unnamed: R21.1, SW5.3, SW5.4
unnamed: R31.1, U4.6
unnamed: R31.2, U4.31
unnamed: R32.2, U4.22
unnamed: R33.2, U4.21
unnamed: R36.1, U5.3
unnamed: R37.1, U5.4
unnamed: R43.1, U27.5
unnamed: R48.1, SW9.6
unnamed: R49.1, SW9.3
unnamed: R69.2, U6.1
unnamed: R70.2, U6.6
unnamed: R71.2, U6.5
unnamed: R72.2, U6.2
unnamed: R73.2, U7.22
unnamed: R74.2, U7.21
unnamed: R95.2, U10.4
unnamed: R114.2, U12.16
unnamed: R115.2, U12.15
unnamed: R116.2, U12.14
unnamed: R117.2, U12.12
unnamed: R126.2, U13.3
unnamed: R130.1, R131.2, R132.2, U15.3
unnamed: R135.1, U15.5, U15.6
unnamed: R158.1, U16.28
unnamed: R159.1, U16.3
unnamed: R160.1, U16.4
unnamed: R161.1, U16.19
unnamed: R161.2, U16.18
unnamed: R162.1, R164.1, U16.16
unnamed: R170.2, R171.2, R172.2, U21.1, U21.48
unnamed: R173.2, R174.1, U22.3
unnamed: R175.2, R176.1, U23.3
unnamed: R177.1, U22.6
unnamed: R178.1, U23.6
unnamed: R179.2, R180.1, U22.5
unnamed: R181.2, R182.1, U23.5
unnamed: R186.1, R192.1, U24.5
unnamed: R187.1, R190.1, U24.24
unnamed: R252.2, R253.2, U14.3
unnamed: U13.1, Y1.1
unnamed: U13.2, Y1.2
VH: CN2.P, P41.1, P42.1, P43.1, P44.1, P45.1, P46.1, P47.1, P48.1, Q8.5
Vbak: C58.1, C59.1, C67.2, C97.2, D15.1, R185.1, U13.8, U16.11, U25.C1
